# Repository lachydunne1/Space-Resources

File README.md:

# Space-Resources
Intial Commit

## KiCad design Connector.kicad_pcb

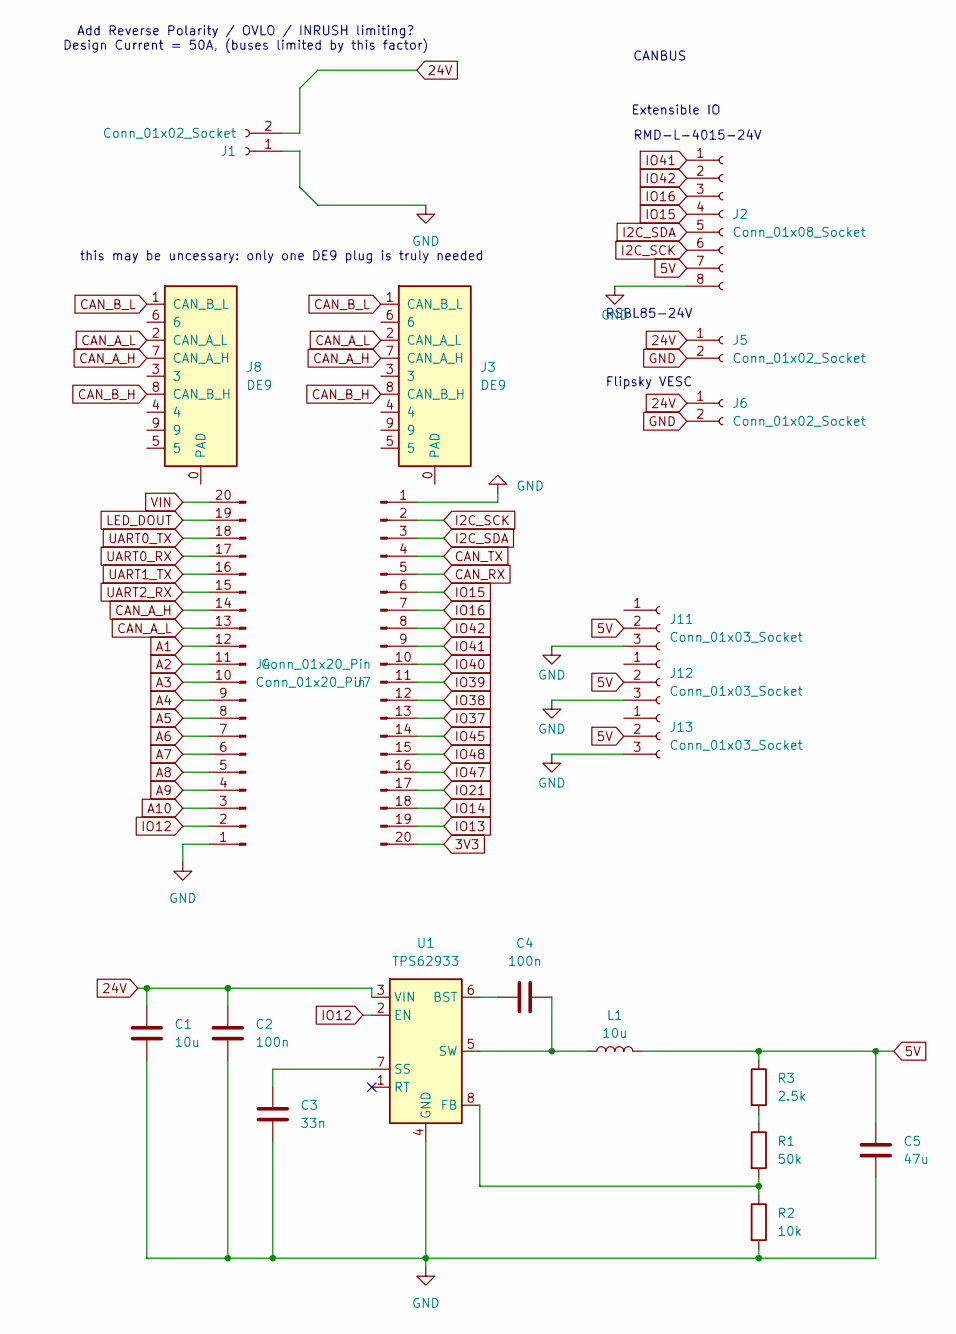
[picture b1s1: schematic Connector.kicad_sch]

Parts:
C1: 10u; C_0603_1608Metric
C2, C4: 100n; C_0603_1608Metric
C3: 33n; C_0603_1608Metric
C5: 47u; C_1808_4520Metric
J1, J5, J6: Conn_01x02_Socket; AMASS_XT90PW-M_1x02_P10.90mm_Horizontal
J2: Conn_01x08_Socket; JST_EH_B8B-EH-A_1x08_P2.50mm_Vertical
J3, J8: DE9; A-DF_09_A_KG-T2S
J4, J7: Conn_01x20_Pin; PinHeader_1x20_P2.54mm_Vertical
J11, J12, J13: Conn_01x03_Socket; JST_EH_B3B-EH-A_1x03_P2.50mm_Vertical
L1: 10u; L_Bourns_SRR1210A
R1: 50k; R_0603_1608Metric_Pad0.98x0.95mm_HandSolder
R2: 10k; R_0603_1608Metric_Pad0.98x0.95mm_HandSolder
R3: 2.5k; R_0603_1608Metric_Pad0.98x0.95mm_HandSolder
U1: TPS62933; SOT-583-8

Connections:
3V3: J7.20
5V: C5.1, J2.7, J11.2, J12.2, J13.2, L1.2, R3.1
24V: C1.1, C2.1, J1.2, J5.1, J6.1, U1.3 (VIN)
A1: J4.12
A2: J4.11
A3: J4.10
A4: J4.9
A5: J4.8
A6: J4.7
A7: J4.6
A8: J4.5
A9: J4.4
A10: J4.3
CAN_A_H: J3.7 (CAN_A_H), J4.14, J8.7 (CAN_A_H)
CAN_A_L: J3.2 (CAN_A_L), J4.13, J8.2 (CAN_A_L)
CAN_B_H: J3.8 (CAN_B_H), J8.8 (CAN_B_H)
CAN_B_L: J3.1 (CAN_B_L), J8.1 (CAN_B_L)
CAN_RX: J7.5
CAN_TX: J7.4
GND: C1.2, C2.2, C3.1, C5.2, J1.1, J2.8, J4.1, J5.2, J6.2, J7.1, J11.3, J12.3, J13.3, R2.2, U1.4 (GND)
I2C_SCK: J2.6, J7.2
I2C_SDA: J2.5, J7.3
IO12: J4.2, U1.2 (EN)
IO13: J7.19
IO14: J7.18
IO15: J2.4, J7.6
IO16: J2.3, J7.7
IO21: J7.17
IO37: J7.13
IO38: J7.12
IO39: J7.11
IO40: J7.10
IO41: J2.1, J7.9
IO42: J2.2, J7.8
IO45: J7.14
IO47: J7.16
IO48: J7.15
LED_DOUT: J4.19
unnamed: R1.1, R3.2
unnamed: C4.1, U1.6 (BST)
unnamed: R1.2, R2.1, U1.8 (FB)
unnamed: C3.2, U1.7 (SS)
unnamed: C4.2, L1.1, U1.5 (SW)
UART0_RX: J4.17
UART0_TX: J4.18
UART1_TX: J4.16
UART2_RX: J4.15
VIN: J4.20

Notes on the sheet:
Extensible IO
this may be uncessary: only one DE9 plug is truly needed
RMD-L-4015-24V
Add Reverse Polarity / OVLO / INRUSH limiting? Design Current = 50A, (buses limited by this factor)
Flipsky VESC
CANBUS
RSBL85-24V

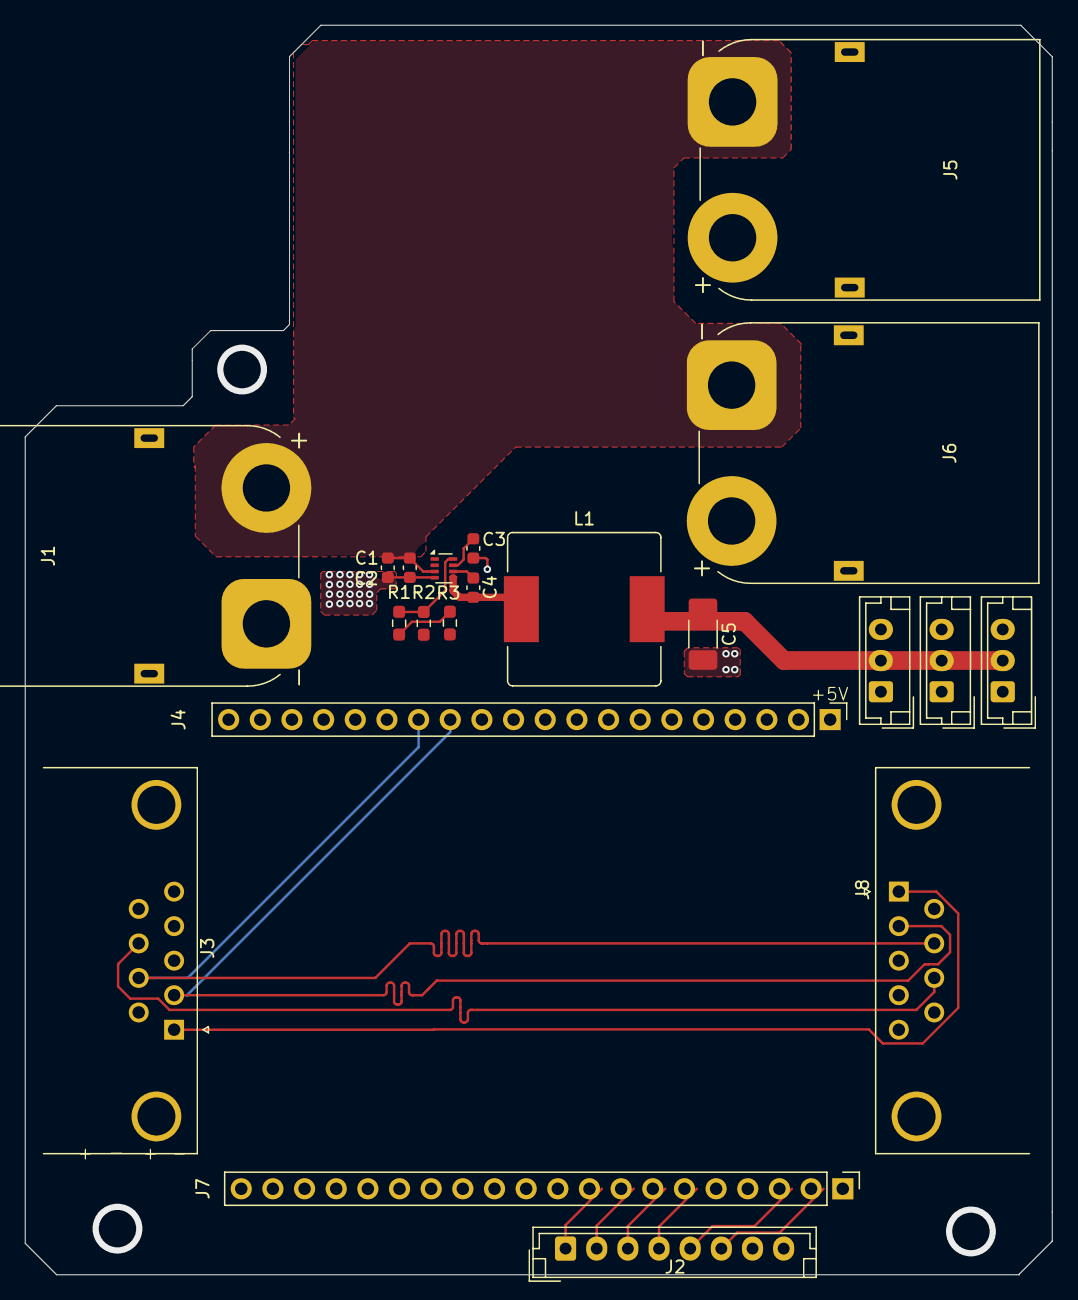
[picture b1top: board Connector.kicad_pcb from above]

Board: 2 copper layers, 82.4 x 100.2 mm, 21 parts (0 on the bottom side), 19 nets.

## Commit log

2025-12-19 init
2025-12-19 added pcb
2026-01-08 Revision V3
    Added low-side switches, UART channel.
